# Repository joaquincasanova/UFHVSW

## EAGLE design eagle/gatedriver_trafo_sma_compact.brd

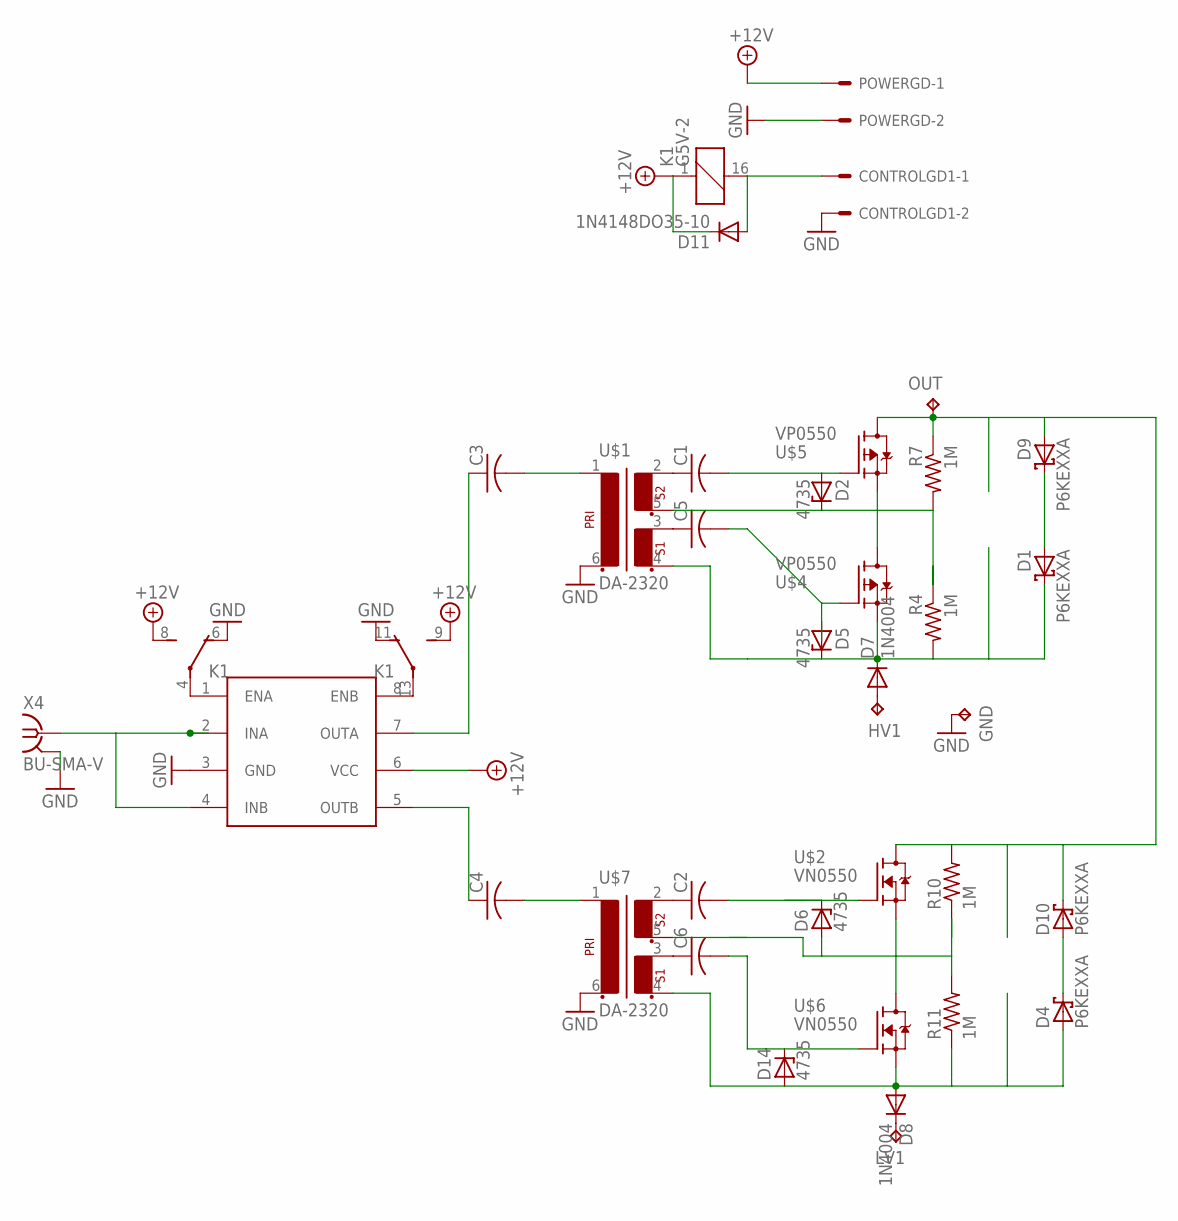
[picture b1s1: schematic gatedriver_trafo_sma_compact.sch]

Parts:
C1, C2, C3, C4, C5, C6: C-US050-055X075; C050-055X075
CONTROLGD1: KK-156-2
D1, D4, D9, D10: P6KEXXA; C1702-15
D2, D5, D6, D14: 4735; ZDIO-10
D7, D8: 1N4004; DO41-10
D11: 1N4148DO35-10; DO35-10
GND: TPPAD1-20Y; P1-20Y
HV1: TPPAD1-20Y; P1-20Y
K1: G5V-2
LV1: TPPAD1-20Y; P1-20Y
OUT: TPPAD1-20Y; P1-20Y
POWERGD: KK-156-2
R4, R7, R10, R11: 1M; 0207/12
U$1, U$7: DA-2320; DIL06
U$2, U$6: VN0550; TO92-
U$3: UCC27425; DIL08
U$4, U$5: VP0550; TO92-
X4: BU-SMA-V

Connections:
+15V: D11.C, K1.1, K1.8 (S), K1.9 (S), POWERGD.1, U$3.6 (VCC)
ENSW: CONTROLGD1.1, D11.A, K1.16 (2)
GND: CONTROLGD1.2, GND.TP, K1.6 (O), K1.11 (O), POWERGD.2, U$1.6 (2), U$3.3 (GND), U$7.6 (2), X4.2, X4.3 (2), X4.4 (2), X4.5 (2)
unnamed: U$3.2 (INA), U$3.4 (INB), X4.1
unnamed: C3.1, U$3.7 (OUTA)
unnamed: C3.2, U$1.1
unnamed: C4.1, U$3.5 (OUTB)
unnamed: C1.1, U$1.2 (6)
unnamed: C4.2, U$7.1
unnamed: C5.1, U$1.3 (4)
unnamed: D9.A, D10.C, OUT.TP, R7.1, R10.2, U$2.1 (D), U$5.1 (D)
unnamed: D8.C, LV1.TP
unnamed: C1.2, D2.A, U$5.2 (G)
unnamed: D1.A, D9.C
unnamed: D4.C, D10.A
unnamed: K1.4, U$3.1 (ENA)
unnamed: K1.13, U$3.8 (ENB)
unnamed: C5.2, D5.A, U$4.2 (G)
unnamed: D1.C, D5.C, D7.C, R4.2, U$1.4 (3), U$4.3 (S)
unnamed: D6.A, R10.1, R11.2, U$2.3 (S), U$6.1 (D)
unnamed: D2.C, R4.1, R7.2, U$1.5, U$4.1 (D), U$5.3 (S)
unnamed: C2.1, U$7.2 (6)
unnamed: C6.1, U$7.3 (4)
unnamed: C2.2, D6.C, U$2.2 (G)
unnamed: C6.2, D14.C, U$6.2 (G)
unnamed: D7.A, HV1.TP
unnamed: D4.A, D8.A, D14.A, R11.1, U$6.3 (S), U$7.4 (3)

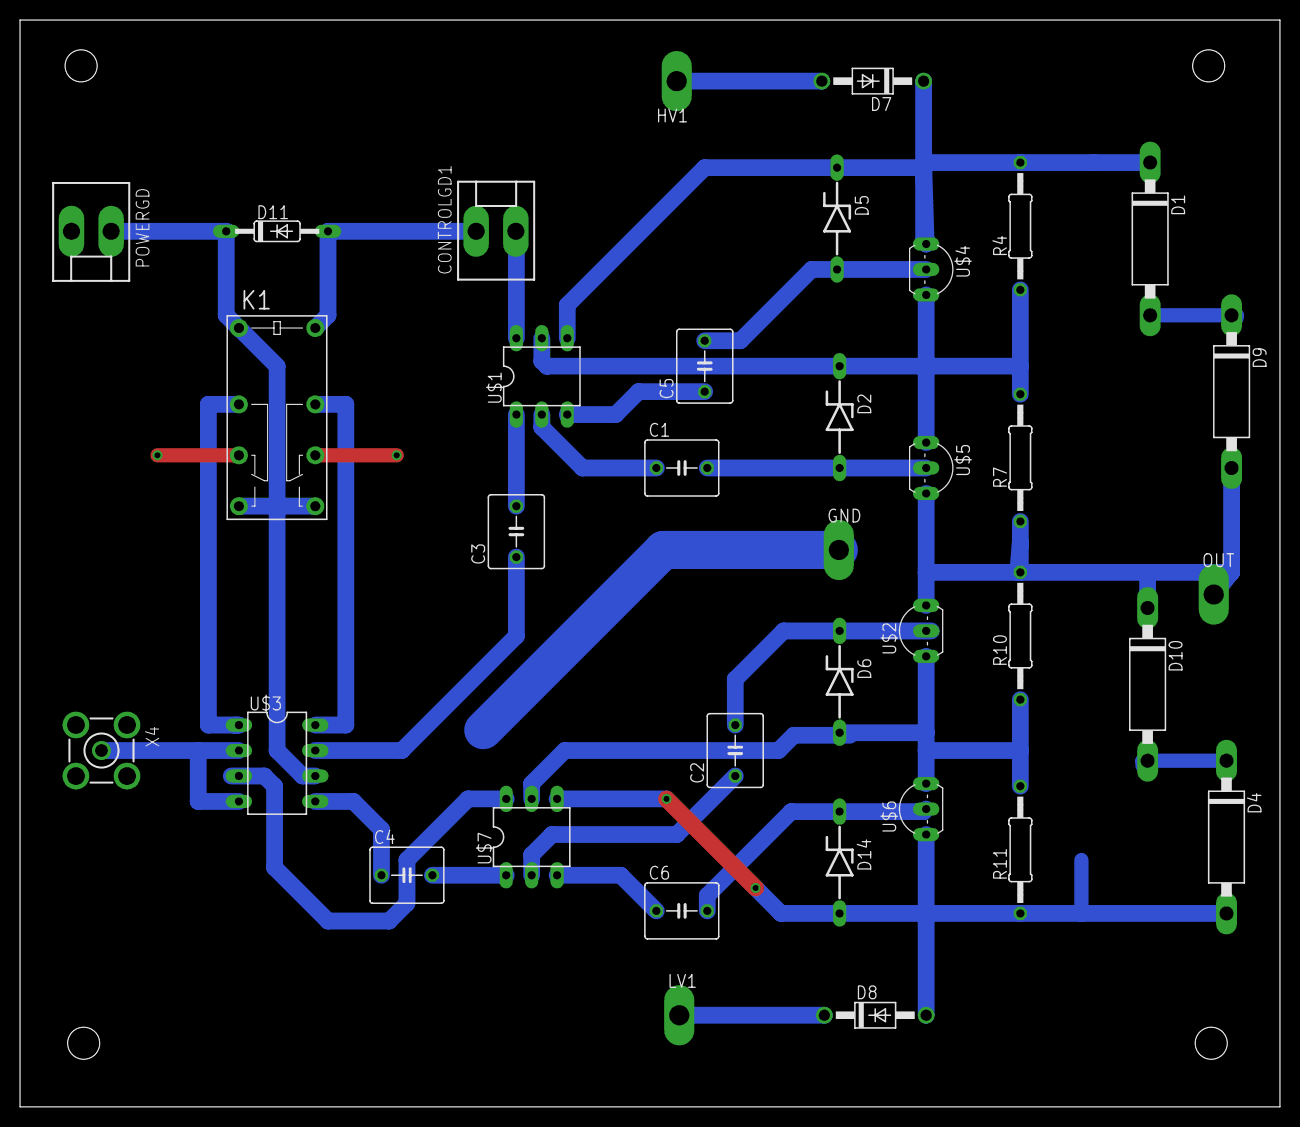
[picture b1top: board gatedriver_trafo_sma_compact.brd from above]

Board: 2 copper layers, 125.7 x 108.5 mm, 36 parts (0 on the bottom side), 27 nets.

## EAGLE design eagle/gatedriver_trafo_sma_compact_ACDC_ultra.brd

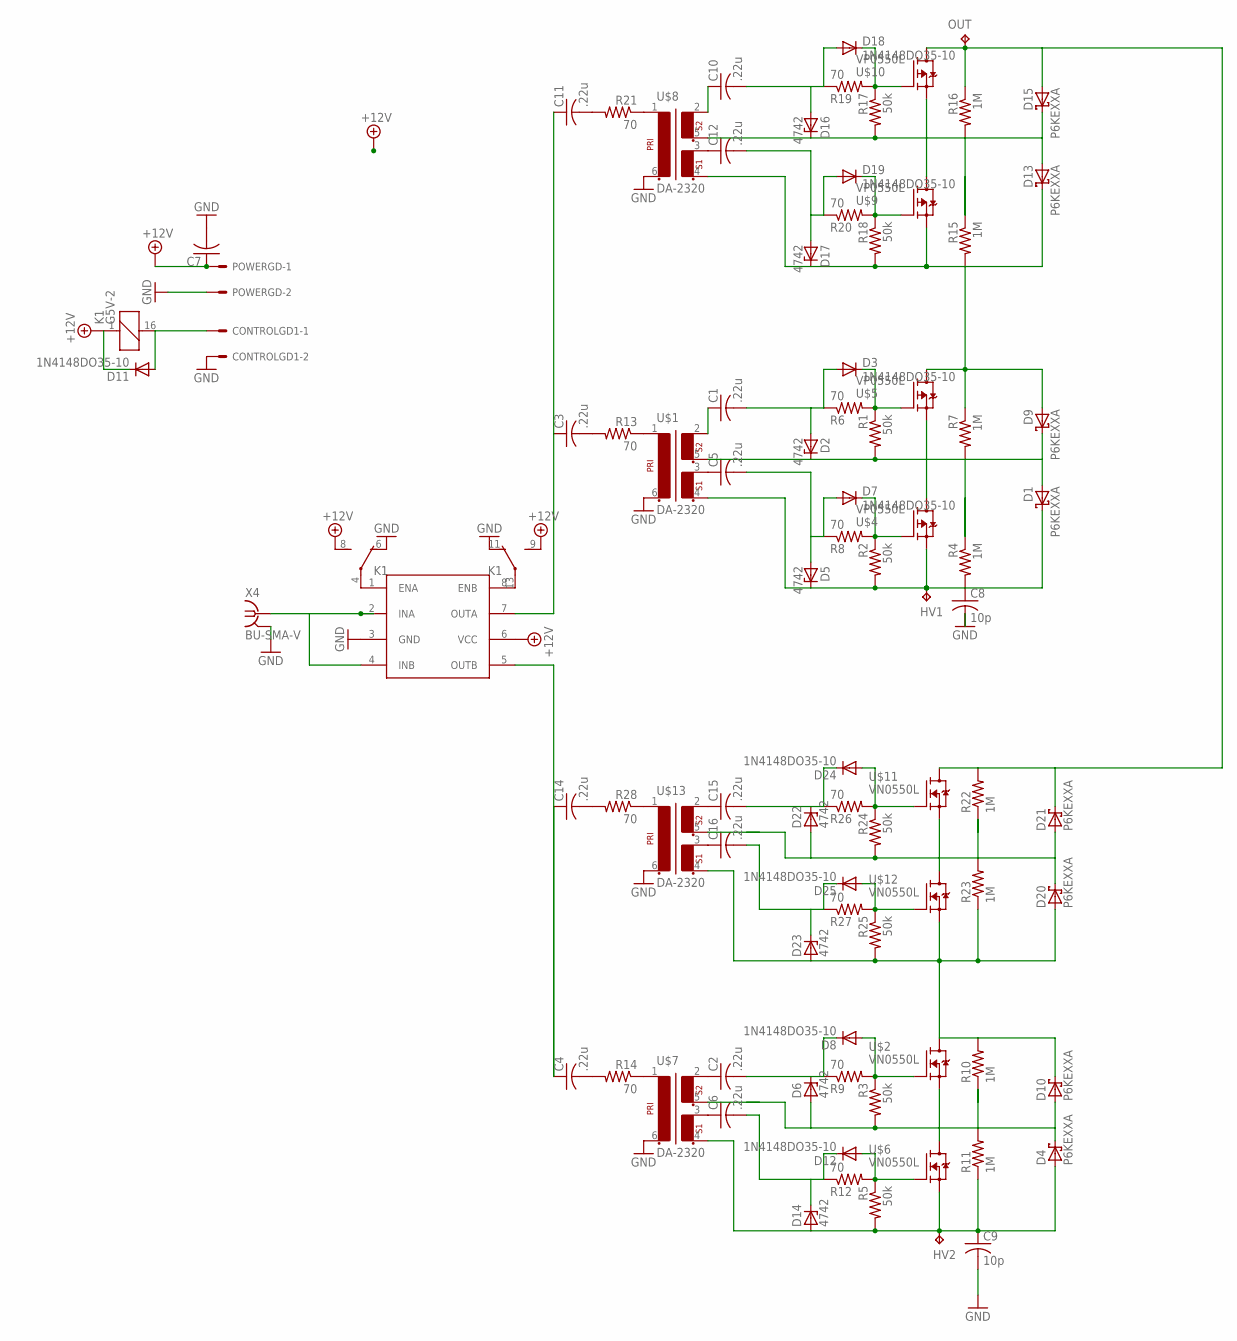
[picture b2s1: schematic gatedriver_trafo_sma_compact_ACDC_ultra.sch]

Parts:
C1, C2, C3, C4, C5, C6, C10, C11, C12, C14, C15, C16: .22u; C050-055X075
C7: C-US050-030X075; C050-030X075
C8, C9: 10p; C102-064X133
CONTROLGD1: KK-156-2
D1, D4, D9, D10, D13, D15, D20, D21: P6KEXXA; C1702-15
D2, D5, D6, D14, D16, D17, D22, D23: 4742; ZDIO-10
D3, D7, D8, D11, D12, D18, D19, D24, D25: 1N4148DO35-10; DO35-10
HV1, HV2: TPPAD1-20Y; P1-20Y
K1: G5V-2
OUT: TPPAD1-20Y; P1-20Y
POWERGD: KK-156-2
R1, R2, R3, R5, R17, R18, R24, R25: 50k; 0207/10
R4, R7, R10, R11, R15, R16, R22, R23: 1M; 0207/10
R6, R8, R9, R12, R13, R14, R19, R20, R21, R26, R27, R28: 70; 0207/10
U$1, U$7, U$8, U$13: DA-2320; DIL06
U$2, U$6, U$11, U$12: VN0550L; TO92L
U$3: UCC27425; DIL08
U$4, U$5, U$9, U$10: VP0550L; TO92L
X4: BU-SMA-V

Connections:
+15V: C7.1, D11.C, K1.1, K1.8 (S), K1.9 (S), POWERGD.1, U$3.6 (VCC)
ENSW: CONTROLGD1.1, D11.A, K1.16 (2)
GND: C7.2, C8.2, C9.2, CONTROLGD1.2, K1.6 (O), K1.11 (O), POWERGD.2, U$1.6 (2), U$3.3 (GND), U$7.6 (2), U$8.6 (2), U$13.6 (2), X4.2, X4.3 (2), X4.4 (2), X4.5 (2)
unnamed: U$3.2 (INA), U$3.4 (INB), X4.1
unnamed: C3.1, C11.1, U$3.7 (OUTA)
unnamed: R13.1, U$1.1
unnamed: C4.1, C14.1, U$3.5 (OUTB)
unnamed: C1.1, U$1.2 (6)
unnamed: R14.1, U$7.1
unnamed: C5.1, U$1.3 (4)
unnamed: D3.C, R1.1, R6.2, U$5.2 (G)
unnamed: C1.2, D2.A, D3.A, R6.1
unnamed: D12.A, R5.1, R12.2, U$6.2 (G)
unnamed: D7.C, R2.1, R8.2, U$4.2 (G)
unnamed: D4.C, D6.A, D10.A, R3.2, R10.1, R11.2, U$2.3 (S), U$6.1 (D)
unnamed: K1.4, U$3.1 (ENA)
unnamed: K1.13, U$3.8 (ENB)
unnamed: C5.2, D5.A, D7.A, R8.1
unnamed: C8.1, D1.C, D5.C, HV1.TP, R2.2, R4.2, U$1.4 (3), U$4.3 (S)
unnamed: D1.A, D2.C, D9.C, R1.2, R4.1, R7.2, U$1.5, U$4.1 (D), U$5.3 (S)
unnamed: C3.2, R13.2
unnamed: C4.2, R14.2
unnamed: C2.1, U$7.2 (6)
unnamed: C6.1, U$7.3 (4)
unnamed: C9.1, D4.A, D14.A, HV2.TP, R5.2, R11.1, U$6.3 (S), U$7.4 (3)
unnamed: C2.2, D6.C, D8.C, R9.1
unnamed: D15.A, D21.C, OUT.TP, R16.1, R22.2, U$10.1 (D), U$11.1 (D)
unnamed: C6.2, D12.C, D14.C, R12.1
unnamed: C10.1, U$8.2 (6)
unnamed: C12.1, U$8.3 (4)
unnamed: C12.2, D17.A, D19.A, R20.1
unnamed: D9.A, D13.C, D17.C, R7.1, R15.2, R18.2, U$5.1 (D), U$8.4 (3), U$9.3 (S)
unnamed: D13.A, D15.C, D16.C, R15.1, R16.2, R17.2, U$8.5, U$9.1 (D), U$10.3 (S)
unnamed: D18.C, R17.1, R19.2, U$10.2 (G)
unnamed: C10.2, D16.A, D18.A, R19.1
unnamed: D19.C, R18.1, R20.2, U$9.2 (G)
unnamed: R21.1, U$8.1
unnamed: C11.2, R21.2
unnamed: C15.1, U$13.2 (6)
unnamed: C16.1, U$13.3 (4)
unnamed: C15.2, D22.C, D24.C, R26.1
unnamed: C16.2, D23.C, D25.C, R27.1
unnamed: D20.C, D21.A, D22.A, R22.1, R23.2, R24.2, U$11.3 (S), U$12.1 (D)
unnamed: D25.A, R25.1, R27.2, U$12.2 (G)
unnamed: R28.1, U$13.1
unnamed: C14.2, R28.2
unnamed: D24.A, R24.1, R26.2, U$11.2 (G)
unnamed: D10.C, D20.A, D23.A, R10.2, R23.1, R25.2, U$2.1 (D), U$12.3 (S), U$13.4 (3)
unnamed: D8.A, R3.1, R9.2, U$2.2 (G)

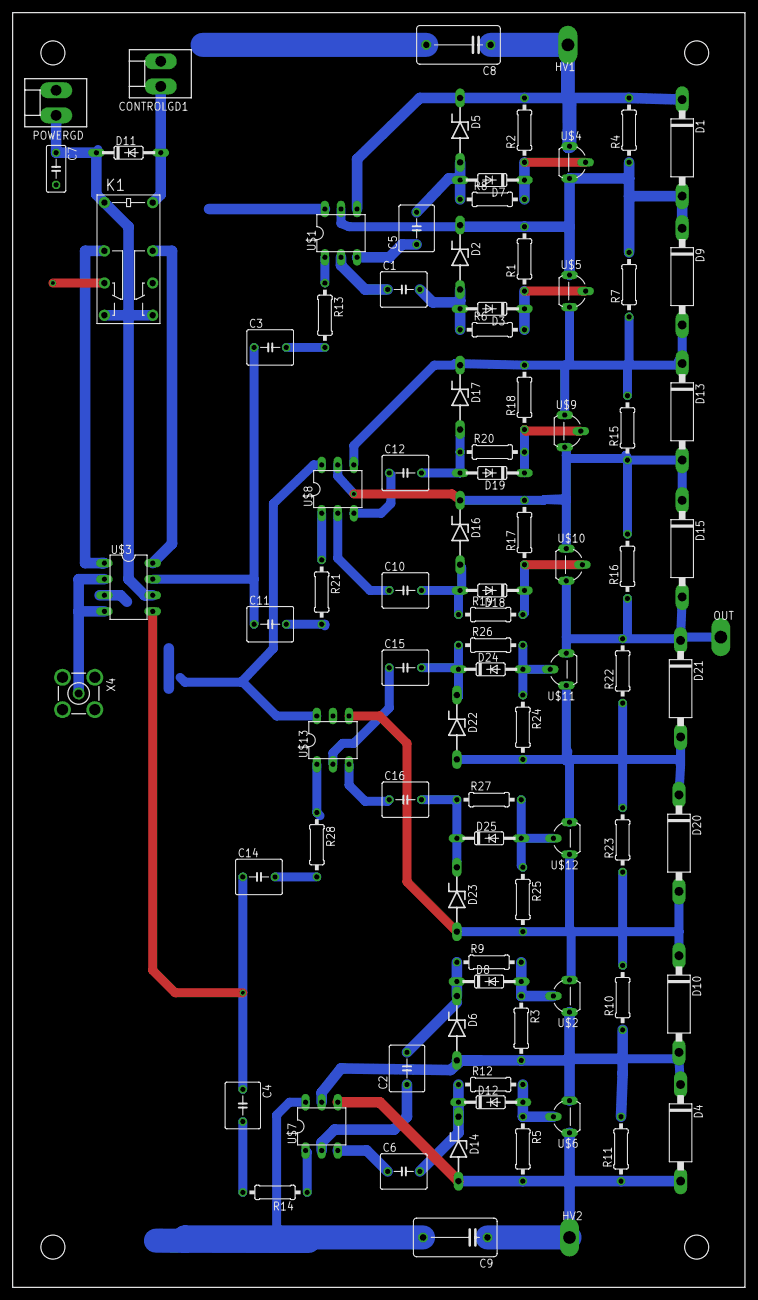
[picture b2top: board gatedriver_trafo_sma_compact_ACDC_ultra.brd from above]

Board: 2 copper layers, 115.6 x 201.2 mm, 88 parts (0 on the bottom side), 49 nets.

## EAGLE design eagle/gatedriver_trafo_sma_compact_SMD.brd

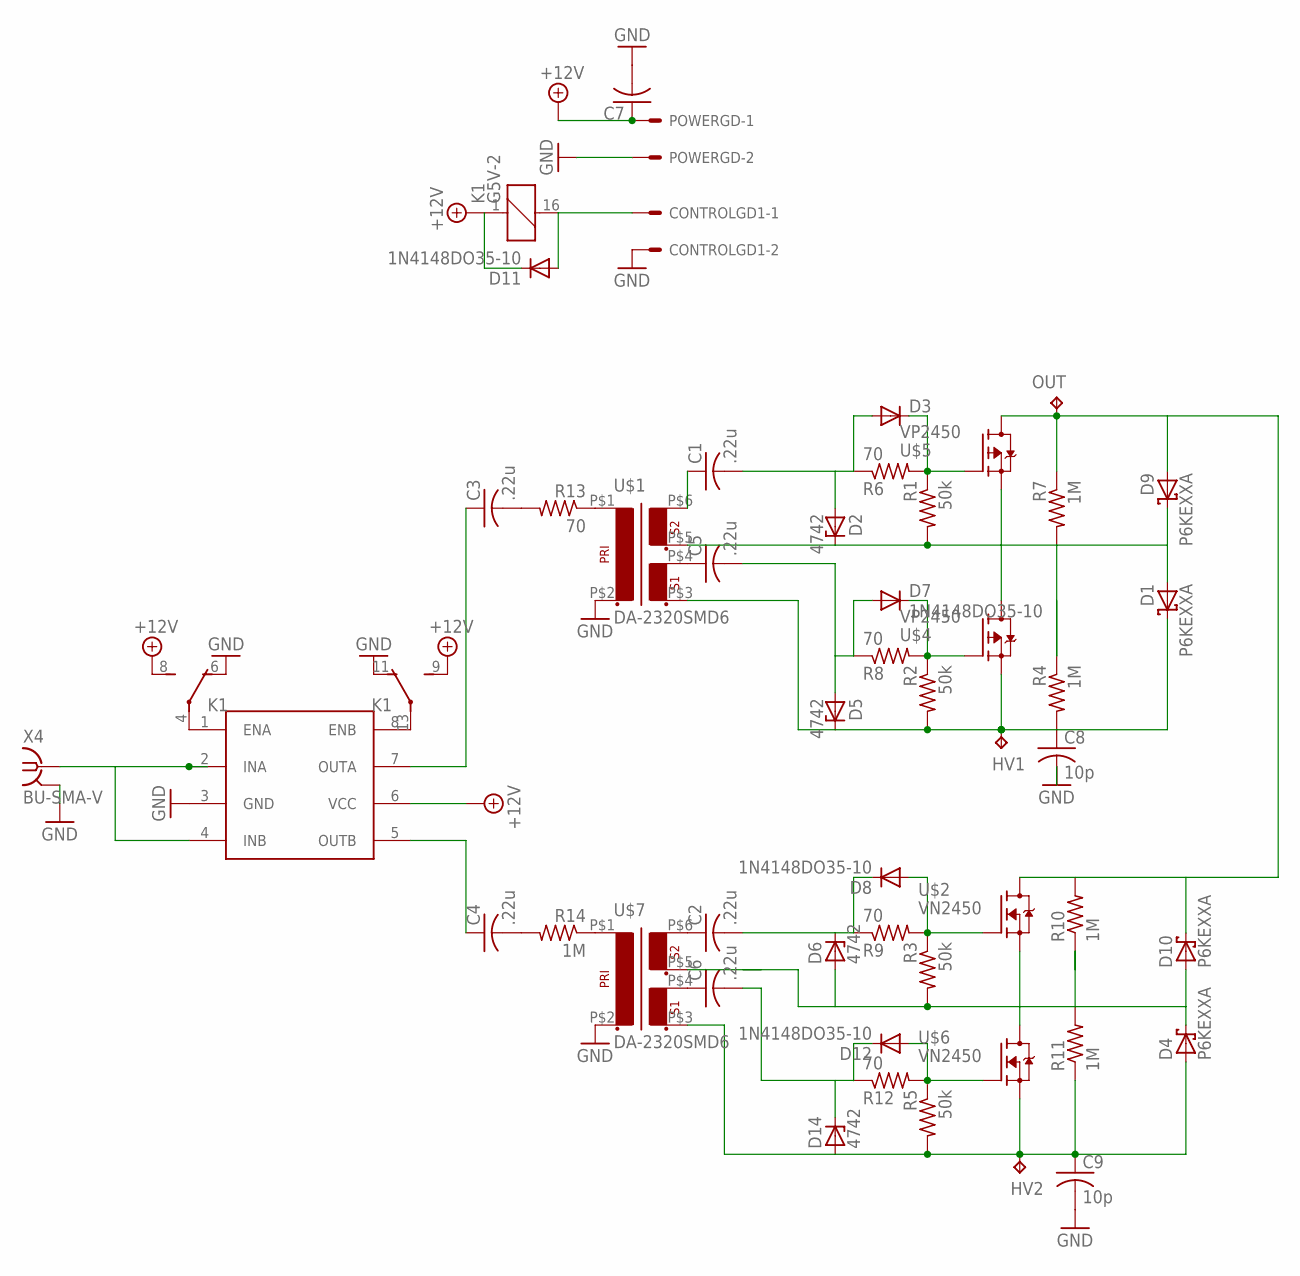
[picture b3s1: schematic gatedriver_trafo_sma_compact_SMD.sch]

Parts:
C1: .22u; C0805
C2, C3, C4, C5, C6: .22u; C050-055X075
C7: C-US050-030X075; C050-030X075
C8, C9: 10p; C102-064X133
CONTROLGD1: KK-156-2
D1, D4, D9, D10: P6KEXXA; C1702-15
D2: 4742; SMB
D3: DIODE-DO214AA; DO214AA
D5, D6, D14: 4742; ZDIO-10
D7, D8, D11, D12: 1N4148DO35-10; DO35-10
HV1, HV2: TPPAD1-20Y; P1-20Y
K1: G5V-2
OUT: TPPAD1-20Y; P1-20Y
POWERGD: KK-156-2
R1: 50k; M0805
R2, R3, R5: 50k; 0207/10
R4, R7, R10, R11, R14: 1M; 0207/10
R6: 70; R0805
R8, R9, R12, R13: 70; 0207/10
U$1, U$7: DA-2320SMD6; SMD6
U$2, U$6: VN2450; SOT89-BCE
U$3: UCC27425; DIL08
U$4, U$5: VP2450; SOT89-BCE
X4: BU-SMA-V

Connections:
+15V: C7.1, D11.C, K1.1, K1.8 (S), K1.9 (S), POWERGD.1, U$3.6 (VCC)
ENSW: CONTROLGD1.1, D11.A, K1.16 (2)
GND: C7.2, C8.2, C9.2, CONTROLGD1.2, K1.6 (O), K1.11 (O), POWERGD.2, U$1.P$2 (2), U$3.3 (GND), U$7.P$2 (2), X4.2, X4.3 (2), X4.4 (2), X4.5 (2)
unnamed: U$3.2 (INA), U$3.4 (INB), X4.1
unnamed: C3.1, U$3.7 (OUTA)
unnamed: R13.1, U$1.P$1 (1)
unnamed: C4.1, U$3.5 (OUTB)
unnamed: C1.1, U$1.P$6 (6)
unnamed: R14.1, U$7.P$1 (1)
unnamed: C5.1, U$1.P$4 (4)
unnamed: D3.C, R1.1, R6.2, U$5.B (G)
unnamed: C1.2, D2.A, D3.A, R6.1
unnamed: D12.A, R5.1, R12.2, U$6.B (G)
unnamed: D7.C, R2.1, R8.2, U$4.B (G)
unnamed: D4.C, D6.A, D10.A, R3.2, R10.1, R11.2, U$2.E (S), U$6.C (D), U$6.C@1 (D)
unnamed: K1.4, U$3.1 (ENA)
unnamed: K1.13, U$3.8 (ENB)
unnamed: C5.2, D5.A, D7.A, R8.1
unnamed: C8.1, D1.C, D5.C, HV1.TP, R2.2, R4.2, U$1.P$3 (3), U$4.E (S)
unnamed: D1.A, D2.C, D9.C, R1.2, R4.1, R7.2, U$1.P$5 (5), U$4.C (D), U$4.C@1 (D), U$5.E (S)
unnamed: C3.2, R13.2
unnamed: C4.2, R14.2
unnamed: D9.A, D10.C, OUT.TP, R7.1, R10.2, U$2.C (D), U$2.C@1 (D), U$5.C (D), U$5.C@1 (D)
unnamed: C2.1, U$7.P$6 (6)
unnamed: C6.1, U$7.P$4 (4)
unnamed: C9.1, D4.A, D14.A, HV2.TP, R5.2, R11.1, U$6.E (S), U$7.P$3 (3)
unnamed: C2.2, D6.C, D8.C, R9.1
unnamed: C6.2, D12.C, D14.C, R12.1
unnamed: D8.A, R3.1, R9.2, U$2.B (G)

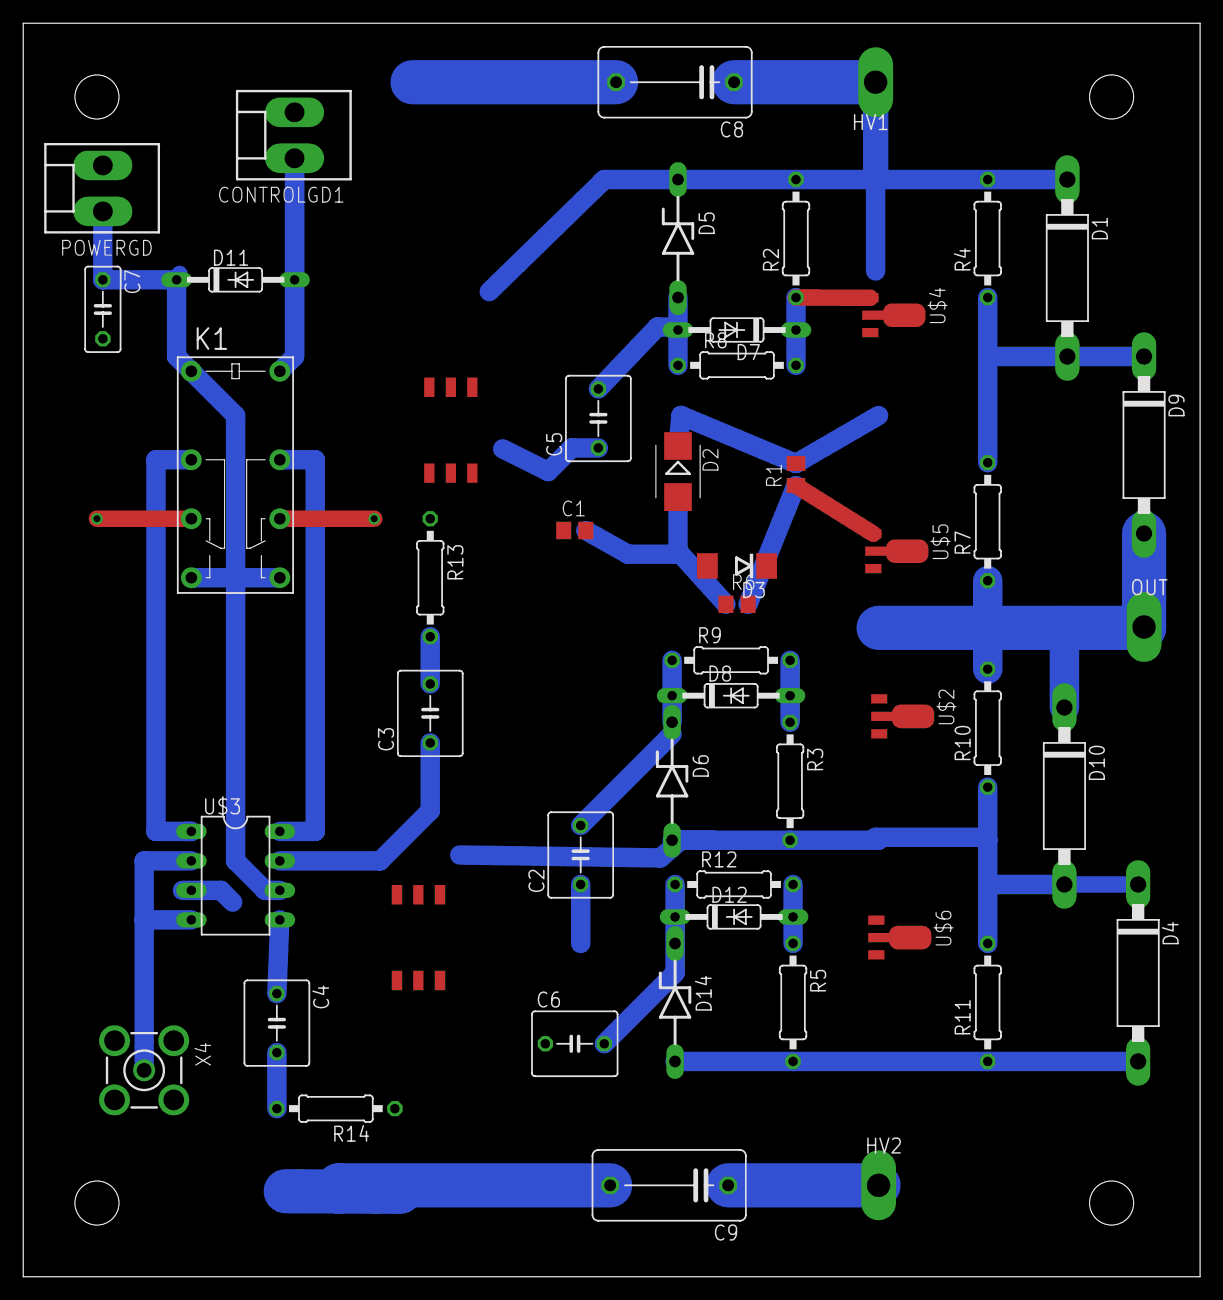
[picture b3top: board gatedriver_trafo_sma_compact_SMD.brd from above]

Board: 2 copper layers, 101.3 x 108.0 mm, 50 parts (0 on the bottom side), 29 nets.

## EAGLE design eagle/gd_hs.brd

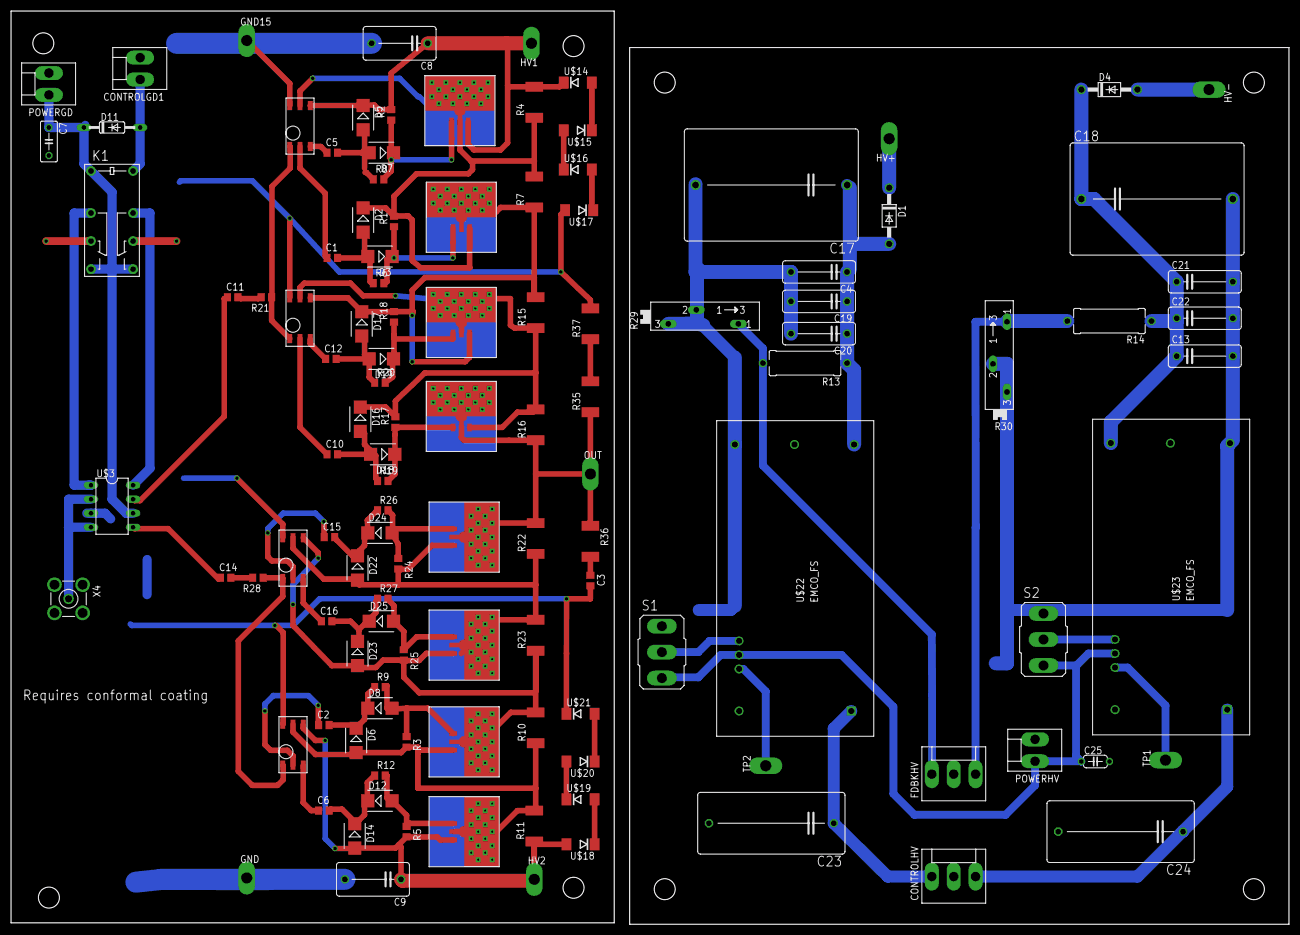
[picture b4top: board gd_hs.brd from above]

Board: 2 copper layers, 231.4 x 165.4 mm, 118 parts (0 on the bottom side), 67 nets.

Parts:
C1, C2, C5, C6, C10, C11, C12, C14, C15, C16: 1u; C0805
C3: 10n; C0805
C4, C13: .01u; C102-043X133
C7: 10n; C050-030X075
C8, C9: 10p; C102-064X133
C17, C18: 1u; C275-205X316
C19, C21: 1n; C102-043X133
C20, C22: 10p; C102-043X133
C23, C24: .1u; C225-113X268
C25: 10n; C050-024X044
CONTROLGD1: KK-156-2
CONTROLHV: KK-156-3
D1, D4: 1N4004; DO41-10
D2, D5, D6, D14, D16, D17, D22, D23: 1SMB5918BT3G; SMB
D3, D7, D8, D12, D18, D19, D24, D25: SMB
D11: 1N4148DO35-10; DO35-10
FDBKHV: KK-156-3
GND, GND15: TPPAD1-20Y; P1-20Y
HV1, HV2: TPPAD1-20Y; P1-20Y
HV+: TPPAD1-20Y; P1-20Y
HV-: TPPAD1-20Y; P1-20Y
K1: G5V-2
OUT: TPPAD1-20Y; P1-20Y
POWERGD: KK-156-2
POWERHV: KK-156-2
R1, R2, R3, R5, R17, R18, R24, R25: 100k; R0805
R4, R7, R10, R11, R15, R16, R22, R23, R35, R36, R37: 10M; R2512
R6, R8, R9, R12, R19, R20, R21, R26, R27, R28: 10; R0805
R13, R14: 2M; P0613/15
R29, R30: SP19L
S1, S2: M9040P
TP1, TP2: PTR1PAD1-20Y; P1-20Y
U$1, U$7, U$8, U$13: DA-2320SMD6; SMD6
U$2, U$6, U$11, U$12: VN2450HS; SO89_HS
U$3: UCC27425; DIL08
U$4, U$5, U$9, U$10: VP2450HS; SO89_HS
U$14, U$15, U$16, U$17, U$18, U$19, U$20, U$21: SMBJ170D-M3/H; DO214AA
U$22, U$23: EMCO-FS10; EMCO-FS
X4: BU-SMA-V

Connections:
+5V: C25.1, POWERHV.1, S1.3, S2.3, U$22.+5, U$23.+5
+15V: C7.1, D11.C, K1.1, K1.8, K1.9, POWERGD.1, U$3.6
ENSW: CONTROLGD1.1, D11.A, K1.16
GND: C3.2, C7.2, C8.2, C9.2, CONTROLGD1.2, GND.TP, GND15.TP, K1.6, K1.11, POWERGD.2, R37.2, U$1.P$6, U$3.3, U$7.P$6, U$8.P$6, U$13.P$6, U$17.A, U$21.C, X4.2, X4.3, X4.4, X4.5
GND1: C4.2, C13.2, C17.2, C18.2, C19.2, C20.2, C21.2, C22.2, C23.2, C24.2, C25.2, CONTROLHV.2, FDBKHV.2, POWERHV.2, R29.E, R29.S, R30.E, R30.S, S1.1, S2.1, U$22.-IN, U$22.-OUT, U$23.+OUT, U$23.-IN
unnamed: U$3.2, U$3.4, X4.1
unnamed: C11.1, U$3.7
unnamed: D16.C, R15.1, R16.2, R17.2, U$8.P$5, U$9.C, U$9.C@1, U$10.E
unnamed: C14.1, U$3.5
unnamed: C1.1, U$1.P$2
unnamed: C8.1, D5.C, HV1.TP, R2.2, R4.2, U$1.P$4, U$4.E, U$14.C
unnamed: C5.1, U$1.P$3
unnamed: D3.C, R1.1, R6.2, U$5.B
unnamed: D2.C, R1.2, R4.1, R7.2, U$1.P$5, U$4.C, U$4.C@1, U$5.E
unnamed: C1.2, D2.A, D3.A, R6.1
unnamed: D12.A, R5.1, R12.2, U$6.B
unnamed: D7.C, R2.1, R8.2, U$4.B
unnamed: C4.1, C17.1, C19.1, C20.1, D1.A, R13.1, U$22.+OUT
unnamed: K1.4, U$3.1
unnamed: K1.13, U$3.8
unnamed: C5.2, D5.A, D7.A, R8.1
unnamed: C13.1, C18.1, C21.1, C22.1, D4.C, R14.1, U$23.-OUT
unnamed: FDBKHV.1, R13.2, R29.A
unnamed: FDBKHV.3, R14.2, R30.A
unnamed: D23.A, R10.2, R23.1, R25.2, U$2.C, U$2.C@1, U$12.E, U$13.P$4
unnamed: D6.A, R3.2, R10.1, R11.2, U$2.E, U$6.C, U$6.C@1, U$7.P$5
unnamed: C2.1, U$7.P$2
unnamed: C6.1, U$7.P$3
unnamed: D1.C, HV+.TP
unnamed: C2.2, D6.C, D8.C, R9.1
unnamed: OUT.TP, R16.1, R22.2, R35.1, R36.1, U$10.C, U$10.C@1, U$11.C, U$11.C@1
unnamed: C6.2, D12.C, D14.C, R12.1
unnamed: C10.1, U$8.P$2
unnamed: C12.1, U$8.P$3
unnamed: C12.2, D17.A, D19.A, R20.1
unnamed: C9.1, D14.A, HV2.TP, R5.2, R11.1, U$6.E, U$7.P$4, U$18.A
unnamed: D4.A, HV-.TP
unnamed: C23.1, CONTROLHV.1, U$22.+IN
unnamed: D18.C, R17.1, R19.2, U$10.B
unnamed: C10.2, D16.A, D18.A, R19.1
unnamed: D19.C, R18.1, R20.2, U$9.B
unnamed: R21.1, U$1.P$1, U$8.P$1
unnamed: C11.2, R21.2
unnamed: C3.1, R36.2
unnamed: C15.1, U$13.P$2
unnamed: C16.1, U$13.P$3
unnamed: C15.2, D22.C, D24.C, R26.1
unnamed: C16.2, D23.C, D25.C, R27.1
unnamed: R35.2, R37.1
unnamed: U$14.A, U$15.C
unnamed: D22.A, R22.1, R23.2, R24.2, U$11.E, U$12.C, U$12.C@1, U$13.P$5
unnamed: D25.A, R25.1, R27.2, U$12.B
unnamed: R28.1, U$7.P$1, U$13.P$1
unnamed: C14.2, R28.2
unnamed: D24.A, R24.1, R26.2, U$11.B
unnamed: C24.1, CONTROLHV.3, U$23.+IN
unnamed: U$15.A, U$16.C
unnamed: U$16.A, U$17.C
unnamed: U$18.C, U$19.A
unnamed: U$19.C, U$20.A
unnamed: U$20.C, U$21.A
unnamed: D17.C, R7.1, R15.2, R18.2, U$5.C, U$5.C@1, U$8.P$4, U$9.E
unnamed: TP1.TP, U$23.ALARM
unnamed: TP2.TP, U$22.ALARM
unnamed: S1.2, U$22.DISABLE
unnamed: S2.2, U$23.DISABLE
unnamed: D8.A, R3.1, R9.2, U$2.B

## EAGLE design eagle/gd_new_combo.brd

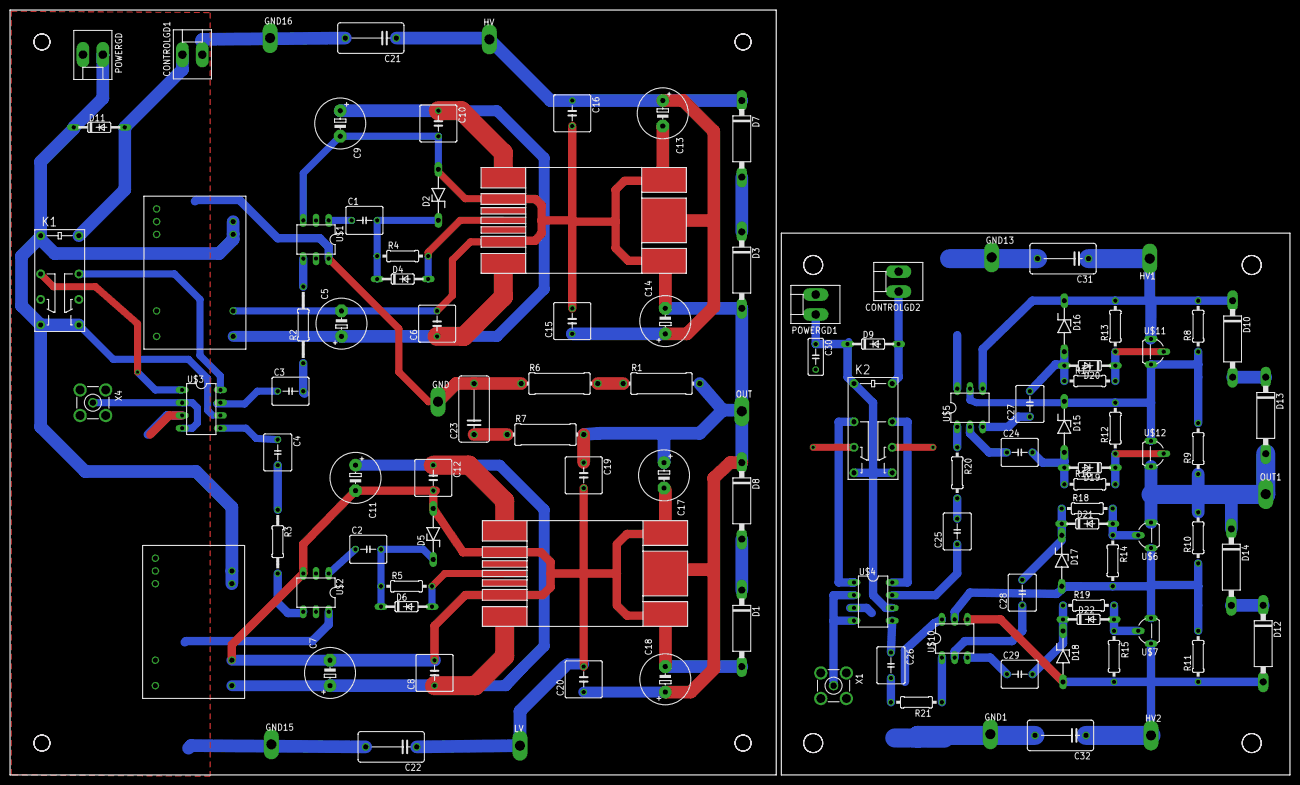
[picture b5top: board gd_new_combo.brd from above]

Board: 2 copper layers, 255.0 x 152.4 mm, 108 parts (0 on the bottom side), 58 nets.

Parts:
C1, C2, C3, C4: C050-055X075
C5, C7, C9, C11, C13, C14, C17, C18: E5-10,5
C6, C8, C10, C12, C15, C16, C19, C20: C050-075X075
C21, C22, C23: C102-064X133
C24, C25, C26, C27, C28, C29: .22u; C050-055X075
C30: C050-030X075
C31, C32: 10p; C102-064X133
CONTROLGD1, CONTROLGD2: KK-156-2
D1, D3, D7, D8, D10, D12, D13, D14: P6KEXXA; C1702-15
D2, D5, D15, D16, D17, D18: 4742; ZDIO-10
D4, D6, D9, D11, D19, D20, D21, D22: 1N4148DO35-10; DO35-10
DC1, DC2: NCS
GND, GND1, GND13, GND15, GND16: TPPAD1-20Y; P1-20Y
HV, HV1, HV2: TPPAD1-20Y; P1-20Y
K1, K2: G5V-2
LV: TPPAD1-20Y; P1-20Y
OUT, OUT1: TPPAD1-20Y; P1-20Y
POWERGD, POWERGD1: KK-156-2
R1, R6, R7: 0414/15
R2: 0207/15
R3: 0207/12
R4, R5: 0207/10
R8, R9, R10, R11, R21: 1M; 0207/10
R12, R13, R14, R15: 50k; 0207/10
R16, R17, R18, R19, R20: 70; 0207/10
U$1, U$2: DA-2319; DIL06
U$3, U$4: UCC27425; DIL08
U$5, U$10: DA-2320; DIL06
U$6, U$7: VN0550L; TO92L
U$8, U$9: IXZ631DF12N100
U$11, U$12: VP0550L; TO92L
X1, X4: BU-SMA-V

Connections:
+12V: D11.C, DC1.P$8, DC1.P$9, DC2.P$8, DC2.P$9, K1.1, K1.8, K1.9, POWERGD.1, U$3.6
+15V: C30.1, D9.C, K2.1, K2.8, K2.9, POWERGD1.1, U$4.6
ENSW: CONTROLGD1.1, D11.A, K1.16
ENSW1: CONTROLGD2.1, D9.A, K2.16
GD_HI: D4.A, R4.2, U$8.P$4
GD_LO: D6.A, R5.2, U$9.P$4
GND: C21.2, C22.2, C23.2, CONTROLGD1.2, DC1.P$2, DC1.P$3, DC2.P$2, DC2.P$3, GND.TP, GND15.TP, GND16.TP, K1.6, K1.11, POWERGD.2, R6.1, U$1.6, U$2.6, U$3.3, X4.2, X4.3, X4.4, X4.5
GND2: C30.2, C31.2, C32.2, CONTROLGD2.2, GND1.TP, GND13.TP, K2.6, K2.11, POWERGD1.2, U$4.3, U$5.6, U$10.6, X1.2, X1.3, X1.4, X1.5
unnamed: U$3.2, U$3.4, X4.1
unnamed: C3.1, U$3.7
unnamed: R2.2, U$1.4
unnamed: C4.1, U$3.5
unnamed: R3.2, U$2.4
unnamed: C4.2, R3.1
unnamed: C5.+, C6.1, C9.+, C10.1, DC1.P$6, U$8.P$1, U$8.P$7
unnamed: C7.+, C8.1, C11.+, C12.1, DC2.P$6, U$9.P$1, U$9.P$7
unnamed: D3.C, D7.A
unnamed: C1.1, U$1.1
unnamed: C2.1, U$2.1
unnamed: R1.1, R6.2
unnamed: C23.1, R7.1
unnamed: K1.4, U$3.1
unnamed: K1.13, U$3.8
unnamed: C3.2, R2.1
unnamed: C13.+, C14.+, C15.1, C16.1, C21.1, D7.C, HV.TP, U$8.P$9
unnamed: D1.C, D8.A
unnamed: C7.-, C8.2, C11.-, C12.2, C17.-, C18.-, C19.2, C20.2, C22.1, D1.A, D5.A, DC2.P$7, LV.TP, U$2.3, U$9.P$2, U$9.P$6, U$9.P$8, U$9.P$10
unnamed: C1.2, D2.C, D4.C, R4.1
unnamed: C2.2, D5.C, D6.C, R5.1
unnamed: U$4.2, U$4.4, X1.1
unnamed: C25.1, U$4.7
unnamed: C26.1, U$4.5
unnamed: K2.4, U$4.1
unnamed: K2.13, U$4.8
unnamed: C24.1, U$5.2
unnamed: C27.1, U$5.3
unnamed: C28.1, U$10.2
unnamed: C29.1, U$10.3
unnamed: C28.2, D17.C, D21.C, R18.1
unnamed: C29.2, D18.C, D22.C, R19.1
unnamed: C27.2, D16.A, D20.A, R17.1
unnamed: C31.1, D10.C, D16.C, HV1.TP, R8.2, R13.2, U$5.4, U$11.3
unnamed: D13.A, D14.C, OUT1.TP, R9.1, R10.2, U$6.1, U$12.1
unnamed: D17.A, R10.1, R11.2, R14.2, U$6.3, U$7.1
unnamed: D15.C, R8.1, R9.2, R12.2, U$5.5, U$11.1, U$12.3
unnamed: D19.C, R12.1, R16.2, U$12.2
unnamed: C24.2, D15.A, D19.A, R16.1
unnamed: D22.A, R15.1, R19.2, U$7.2
unnamed: D20.C, R13.1, R17.2, U$11.2
unnamed: R20.1, U$5.1
unnamed: R21.1, U$10.1
unnamed: C25.2, R20.2
unnamed: C26.2, R21.2
unnamed: C32.1, D12.A, D18.A, HV2.TP, R11.1, R15.2, U$7.3, U$10.4
unnamed: D10.A, D13.C
unnamed: D12.C, D14.A
unnamed: D21.A, R14.1, R18.2, U$6.2
OUT: C5.-, C6.2, C9.-, C10.2, C13.-, C14.-, C15.2, C16.2, C17.+, C18.+, C19.1, C20.1, D2.A, D3.A, D8.C, DC1.P$7, OUT.TP, R1.2, R7.2, U$1.3, U$8.P$2, U$8.P$6, U$8.P$8, U$8.P$10, U$9.P$9
